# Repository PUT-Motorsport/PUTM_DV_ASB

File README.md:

# PUTM_DV_ASB_2023
Autonomus Brake System PCB and Software for PM07

Functionality:
Solenoid valves control,
Pressure sensors data acquisition,
Functional safety, and hard-wired logic implementation,
Autonomous System SDC driver,
RES communication bridge.

Important links:

FSG Rules:
fsg.one/rules

Previous board (unusable)

ASF Examples:
https://www.formulastudent.de/academy/hands-on/asf/

FSG Academy:
https://www.formulastudent.de/fileadmin/user_upload/all/2022/important_docs/FSG21_AS_Beginners_Guide_v1.0.pdf

Jakub's Mechanical construction:
https://files.podio.com/1561594165

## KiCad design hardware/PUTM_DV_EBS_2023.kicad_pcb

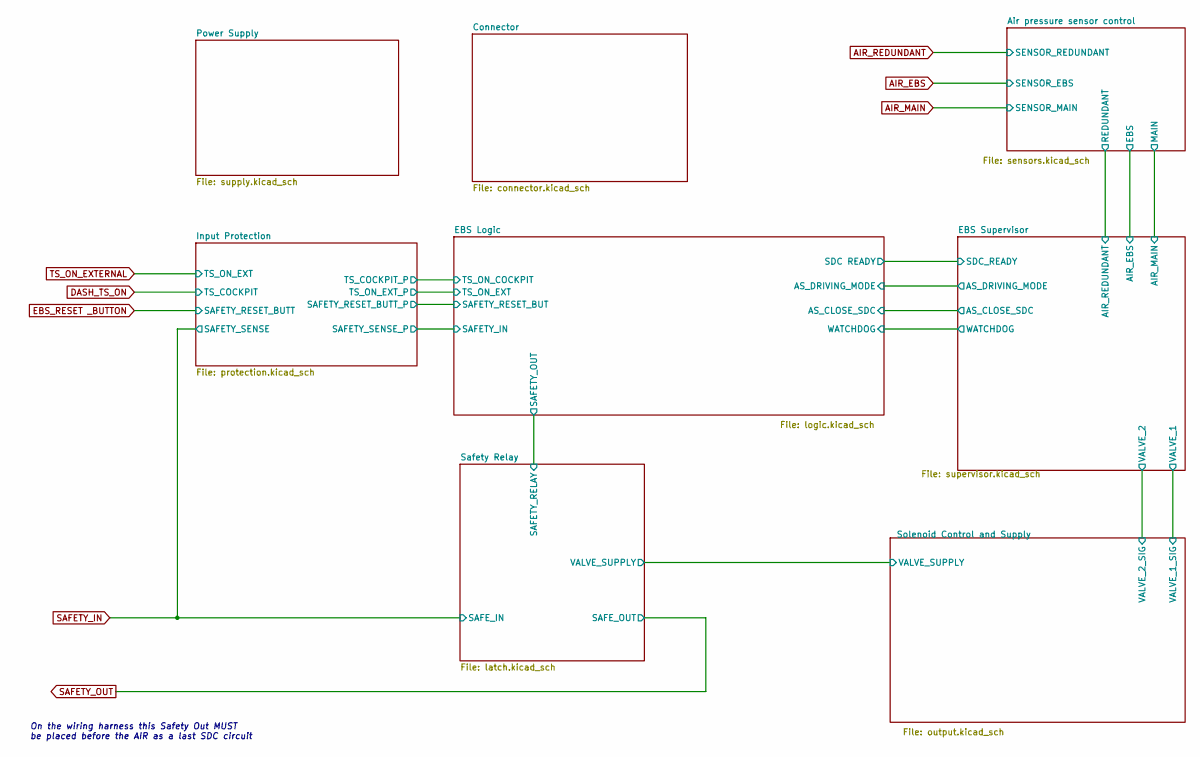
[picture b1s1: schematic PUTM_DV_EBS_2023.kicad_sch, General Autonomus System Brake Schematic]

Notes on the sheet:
On the wiring harness this Safety Out MUST be placed before the AIR as a last SDC circuit

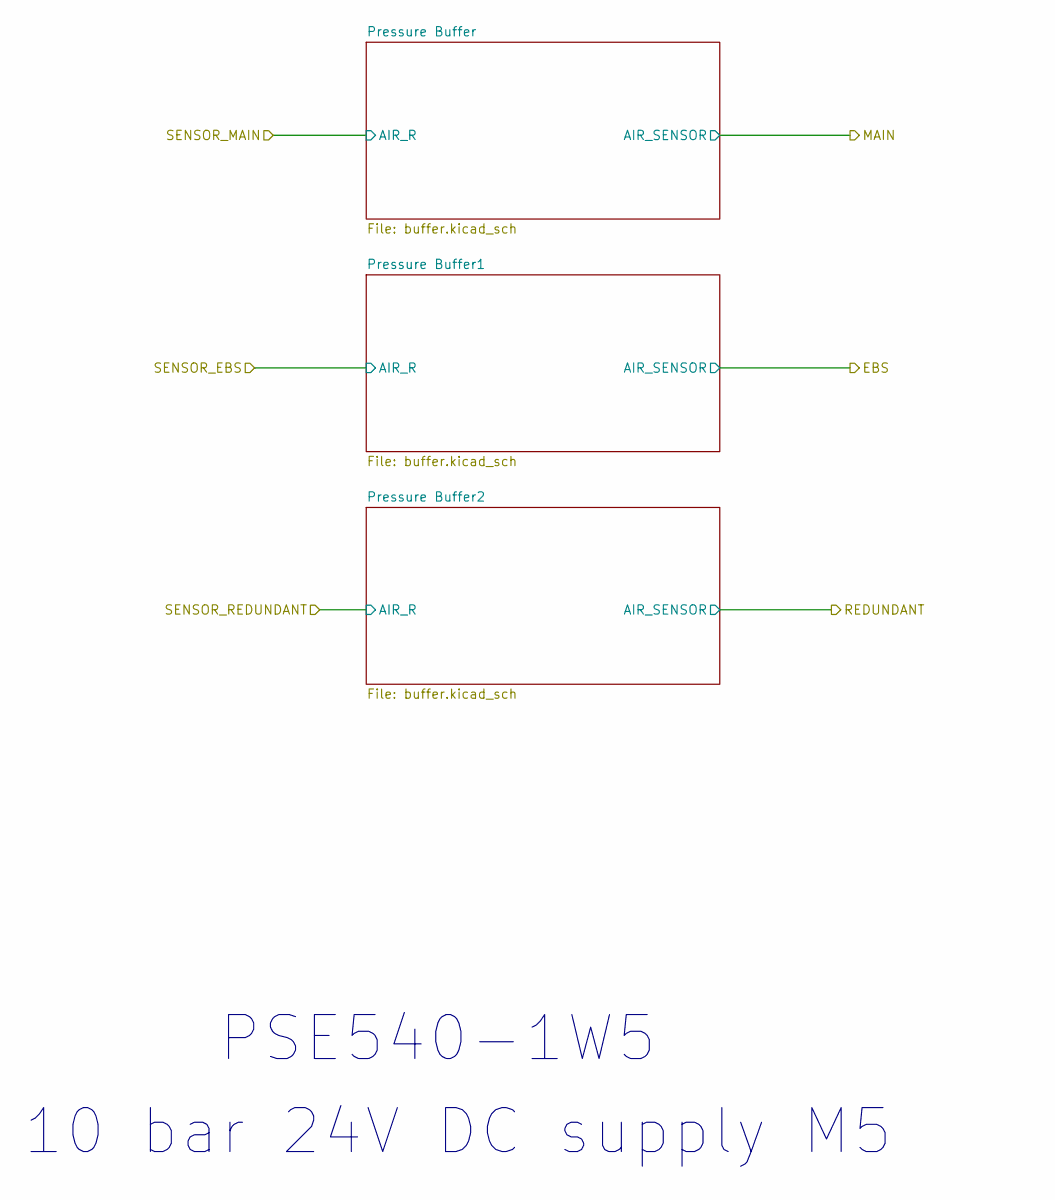
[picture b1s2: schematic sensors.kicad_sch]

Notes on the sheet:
10 bar 24V DC supply M5
PSE540-1W5

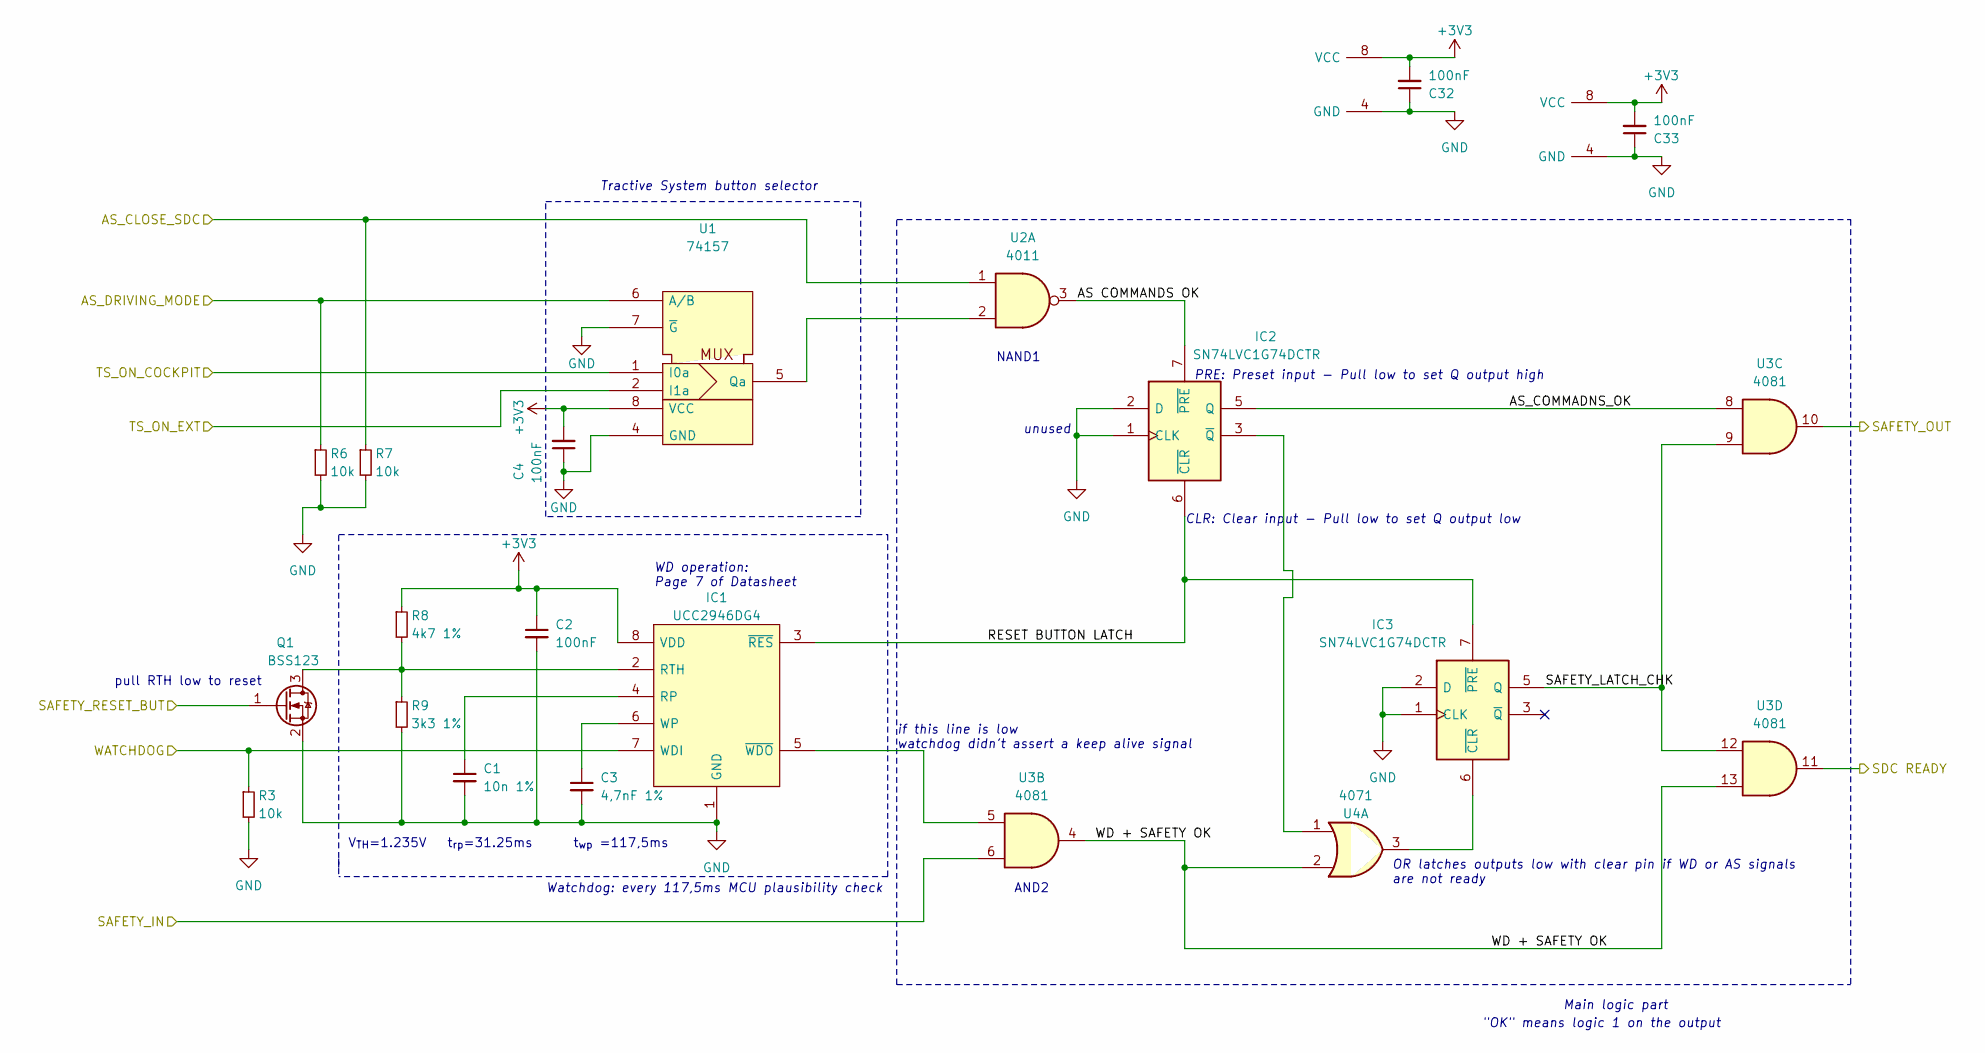
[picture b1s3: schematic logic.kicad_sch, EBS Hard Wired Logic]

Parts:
C1: 10n 1%; C_0603_1608Metric_Pad1.08x0.95mm_HandSolder
C2, C4, C32, C33: 100nF; C_0603_1608Metric_Pad1.08x0.95mm_HandSolder
C3: 4,7nF 1%; C_0603_1608Metric_Pad1.08x0.95mm_HandSolder
IC1: UCC2946DG4; SOIC127P600X175-8N; Mouser Part Number 595-UCC2946DG4
IC2, IC3: SN74LVC1G74DCTR; SOP65P400X130-8N; Mouser Part Number 595-SN74LVC1G74DCTR
Q1: BSS123; SOT-23
R3, R6, R7: 10k; R_0603_1608Metric_Pad0.98x0.95mm_HandSolder
R8: 4k7 1%; R_0603_1608Metric_Pad0.98x0.95mm_HandSolder
R9: 3k3 1%; R_0603_1608Metric_Pad0.98x0.95mm_HandSolder
U1: 74157; VSSOP-8_2.3x2mm_P0.5mm
U2: 4011; TSSOP-14_4.4x5mm_P0.65mm
U3: 4081; TSSOP-14_4.4x5mm_P0.65mm
U4: 4071; TSSOP-14_4.4x5mm_P0.65mm

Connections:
+3V3: C2.1, C4.2, C32.2, C33.2, IC1.8 (VDD), IC2.8 (VCC), IC3.8 (VCC), R8.1, U1.8 (VCC); also elsewhere on the board
/EBS Logic/AS COMMANDS OK: IC2.7 (~PRE), U2.3; also elsewhere on the board
/EBS Logic/AS_CLOSE_SDC: R7.1, U2.1; also elsewhere on the board
/EBS Logic/AS_COMMADNS_OK: IC2.5 (Q), U3.8
/EBS Logic/AS_DRIVING_MODE: R6.1, U1.6 (A/B); also elsewhere on the board
/EBS Logic/RESET BUTTON LATCH: IC1.3 (~RES), IC2.6 (~CLR), IC3.7 (~PRE); also elsewhere on the board
/EBS Logic/SAFETY_IN: U3.6; also elsewhere on the board
/EBS Logic/SAFETY_LATCH_CHK: IC3.5 (Q), U3.9, U3.12; also elsewhere on the board
/EBS Logic/SAFETY_OUT: U3.10; also elsewhere on the board
/EBS Logic/SAFETY_RESET_BUT: Q1.1 (G); also elsewhere on the board
/EBS Logic/SDC READY: U3.11; also elsewhere on the board
/EBS Logic/TS_ON_COCKPIT: U1.1 (I0a); also elsewhere on the board
/EBS Logic/TS_ON_EXT: U1.2 (I1a); also elsewhere on the board
/EBS Logic/WATCHDOG: IC1.7 (WDI), R3.1; also elsewhere on the board
/EBS Logic/WD + SAFETY OK: U3.4, U3.13, U4.2; also elsewhere on the board
GND: C1.2, C2.2, C3.2, C4.1, C32.1, C33.1, IC1.1 (GND), IC2.1 (CLK), IC2.2 (D), IC2.4 (GND), IC3.1 (CLK), IC3.2 (D), IC3.4 (GND), Q1.2 (S), R3.2, R6.2, R7.2, R9.2, U1.4 (GND), U1.7 (~G); also elsewhere on the board
unnamed: C1.1, IC1.4 (RP)
unnamed: C3.1, IC1.6 (WP)
unnamed 65: IC1.2 (RTH), Q1.3 (D), R8.2, R9.1; also elsewhere on the board
unnamed 66: IC1.5 (~WDO), U3.5; also elsewhere on the board
unnamed: IC2.3 (~Q), U4.1
unnamed: IC3.6 (~CLR), U4.3
unnamed: U1.5 (Qa), U2.2

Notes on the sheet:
OR latches outputs low with clear pin if WD or AS signals are not ready
unused
V_{TH}=1.235V
"OK" means logic 1 on the output
Watchdog: every 117,5ms MCU plausibility check
Tractive System button selector
pull RTH low to reset
PRE: Preset input − Pull low to set Q output high
Main logic part
CLR: Clear input − Pull low to set Q output low
AND2
NAND1
WD operation: Page 7 of Datasheet
if this line is low watchdog didn't assert a keep alive signal
t_{wp} =117,5ms
t_{rp}=31.25ms

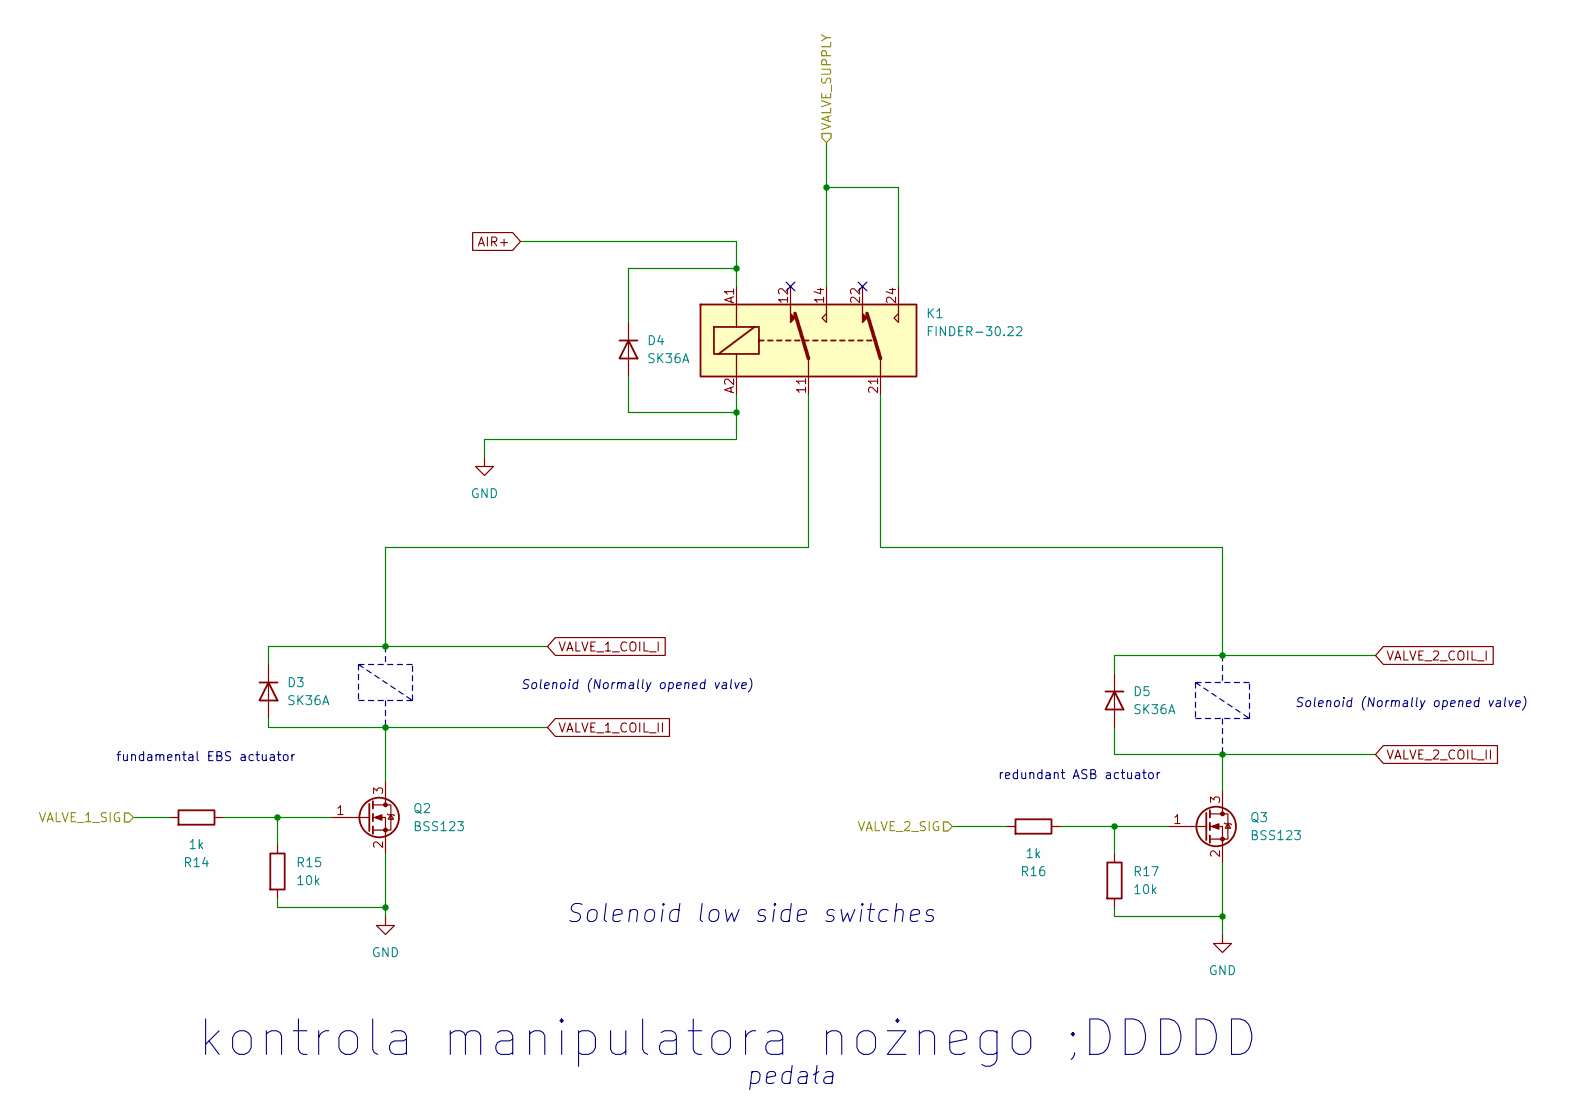
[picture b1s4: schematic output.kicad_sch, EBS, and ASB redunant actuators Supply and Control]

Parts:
D3, D4, D5: SK36A; D_SMA_Handsoldering
K1: FINDER-30.22; Relay_DPDT_Finder_30.22
Q2, Q3: BSS123; SOT-23
R14, R16: 1k; R_0603_1608Metric_Pad0.98x0.95mm_HandSolder
R15, R17: 10k; R_0603_1608Metric_Pad0.98x0.95mm_HandSolder

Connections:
/EBS Supervisor/VALVE_1: R14.2; also elsewhere on the board
/EBS Supervisor/VALVE_2: R16.2; also elsewhere on the board
/Safety Relay/VALVE_SUPPLY: K1.14, K1.24; also elsewhere on the board
AIR+: D4.1 (K), K1.A1; also elsewhere on the board
GND: D4.2 (A), K1.A2, Q2.2 (S), Q3.2 (S), R15.2, R17.2; also elsewhere on the board
unnamed: Q2.1 (G), R14.1, R15.1
unnamed: Q3.1 (G), R16.1, R17.1
VALVE_1_COIL_I: D3.1 (K), K1.11; also elsewhere on the board
VALVE_1_COIL_II: D3.2 (A), Q2.3 (D); also elsewhere on the board
VALVE_2_COIL_I: D5.1 (K), K1.21; also elsewhere on the board
VALVE_2_COIL_II: D5.2 (A), Q3.3 (D); also elsewhere on the board

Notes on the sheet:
Solenoid (Normally opened valve)
Solenoid low side switches
fundamental EBS actuator
pedała
redundant ASB actuator
kontrola manipulatora nożnego ;DDDDD

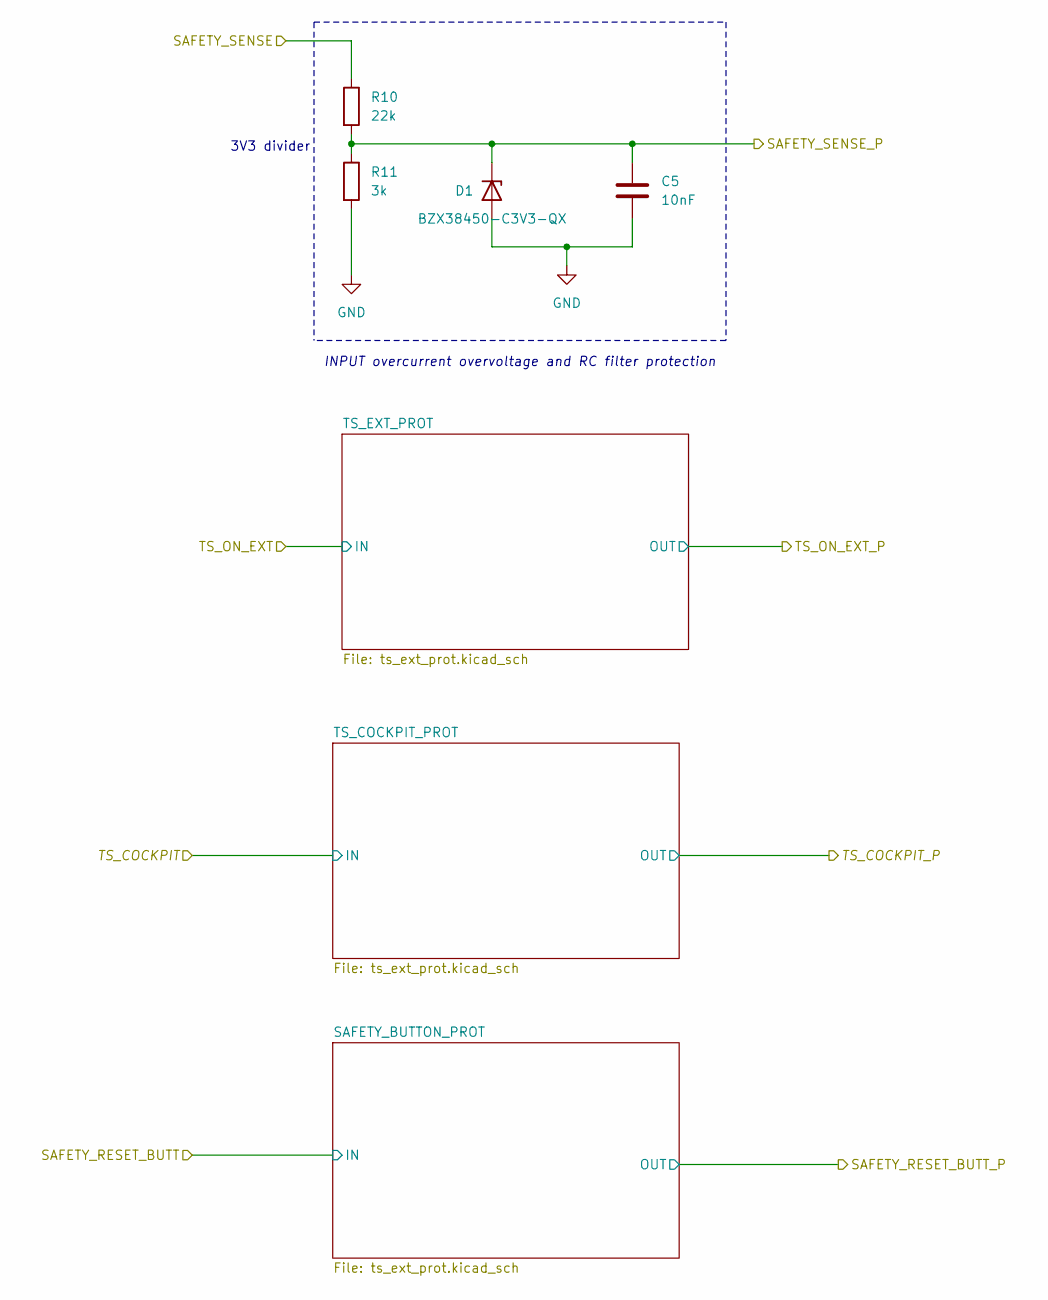
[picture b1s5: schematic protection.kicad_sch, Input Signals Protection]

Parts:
C5: 10nF; C_0603_1608Metric_Pad1.08x0.95mm_HandSolder
D1: BZX38450-C3V3-QX; D_SOD-323_HandSoldering
R10: 22k; R_0603_1608Metric_Pad0.98x0.95mm_HandSolder
R11: 3k; R_0603_1608Metric_Pad0.98x0.95mm_HandSolder

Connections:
/EBS Logic/SAFETY_IN: C5.1, D1.1 (K), R10.2, R11.1; also elsewhere on the board
GND: C5.2, D1.2 (A), R11.2; also elsewhere on the board
SAFETY_IN: R10.1; also elsewhere on the board

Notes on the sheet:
3V3 divider
INPUT overcurrent overvoltage and RC filter protection

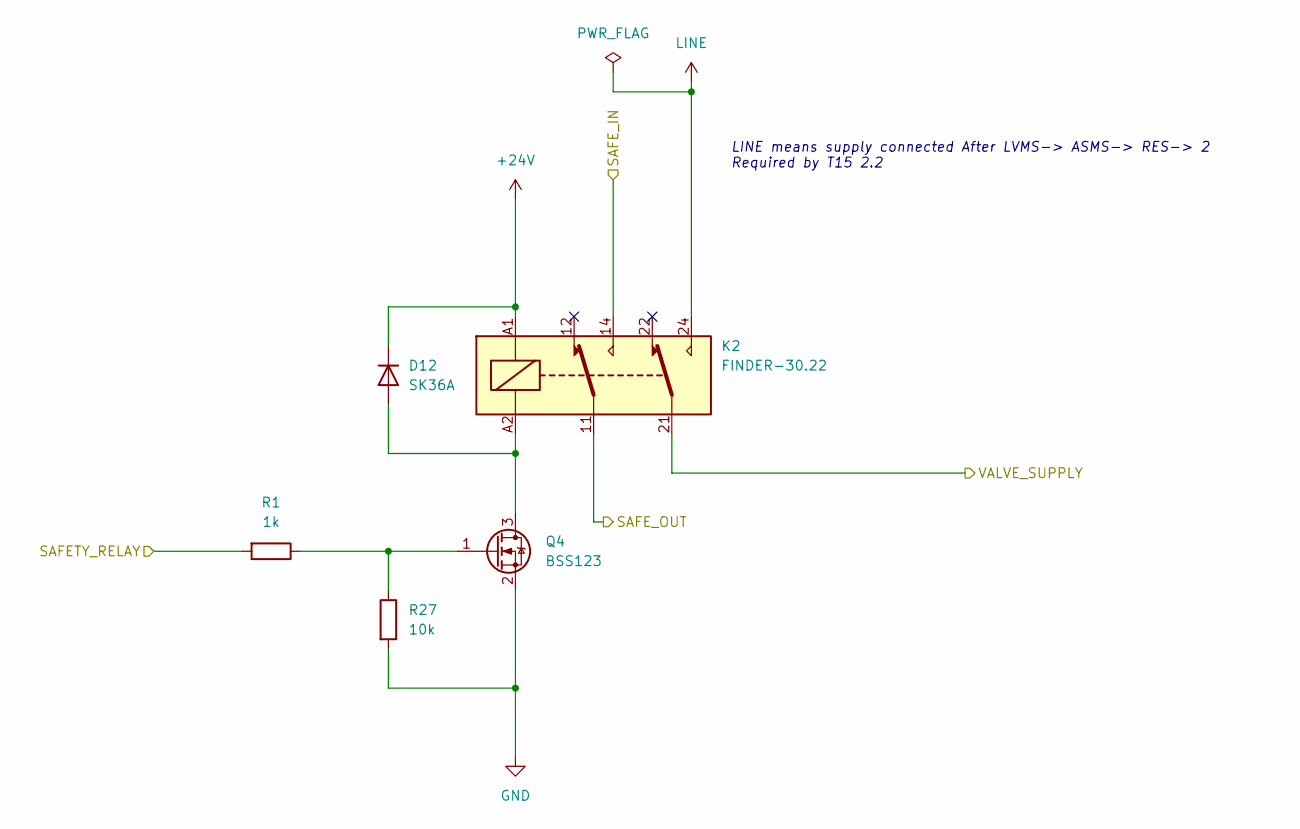
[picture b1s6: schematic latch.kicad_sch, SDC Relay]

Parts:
D12: SK36A; D_SMA_Handsoldering
K2: FINDER-30.22; Relay_DPDT_Finder_30.22
Q4: BSS123; SOT-23
R1: 1k; R_0603_1608Metric_Pad0.98x0.95mm_HandSolder
R27: 10k; R_0603_1608Metric_Pad0.98x0.95mm_HandSolder

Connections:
+24V: D12.1 (K), K2.A1; also elsewhere on the board
/EBS Logic/SAFETY_OUT: R1.2; also elsewhere on the board
/Safety Relay/VALVE_SUPPLY: K2.21; also elsewhere on the board
GND: Q4.2 (S), R27.2; also elsewhere on the board
LINE: K2.24; also elsewhere on the board
unnamed: D12.2 (A), K2.A2, Q4.3 (D)
unnamed: Q4.1 (G), R1.1, R27.1
SAFETY_IN: K2.14; also elsewhere on the board
SAFETY_OUT: K2.11; also elsewhere on the board

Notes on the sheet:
LINE means supply connected After LVMS-> ASMS-> RES-> 2 Required by T15 2.2

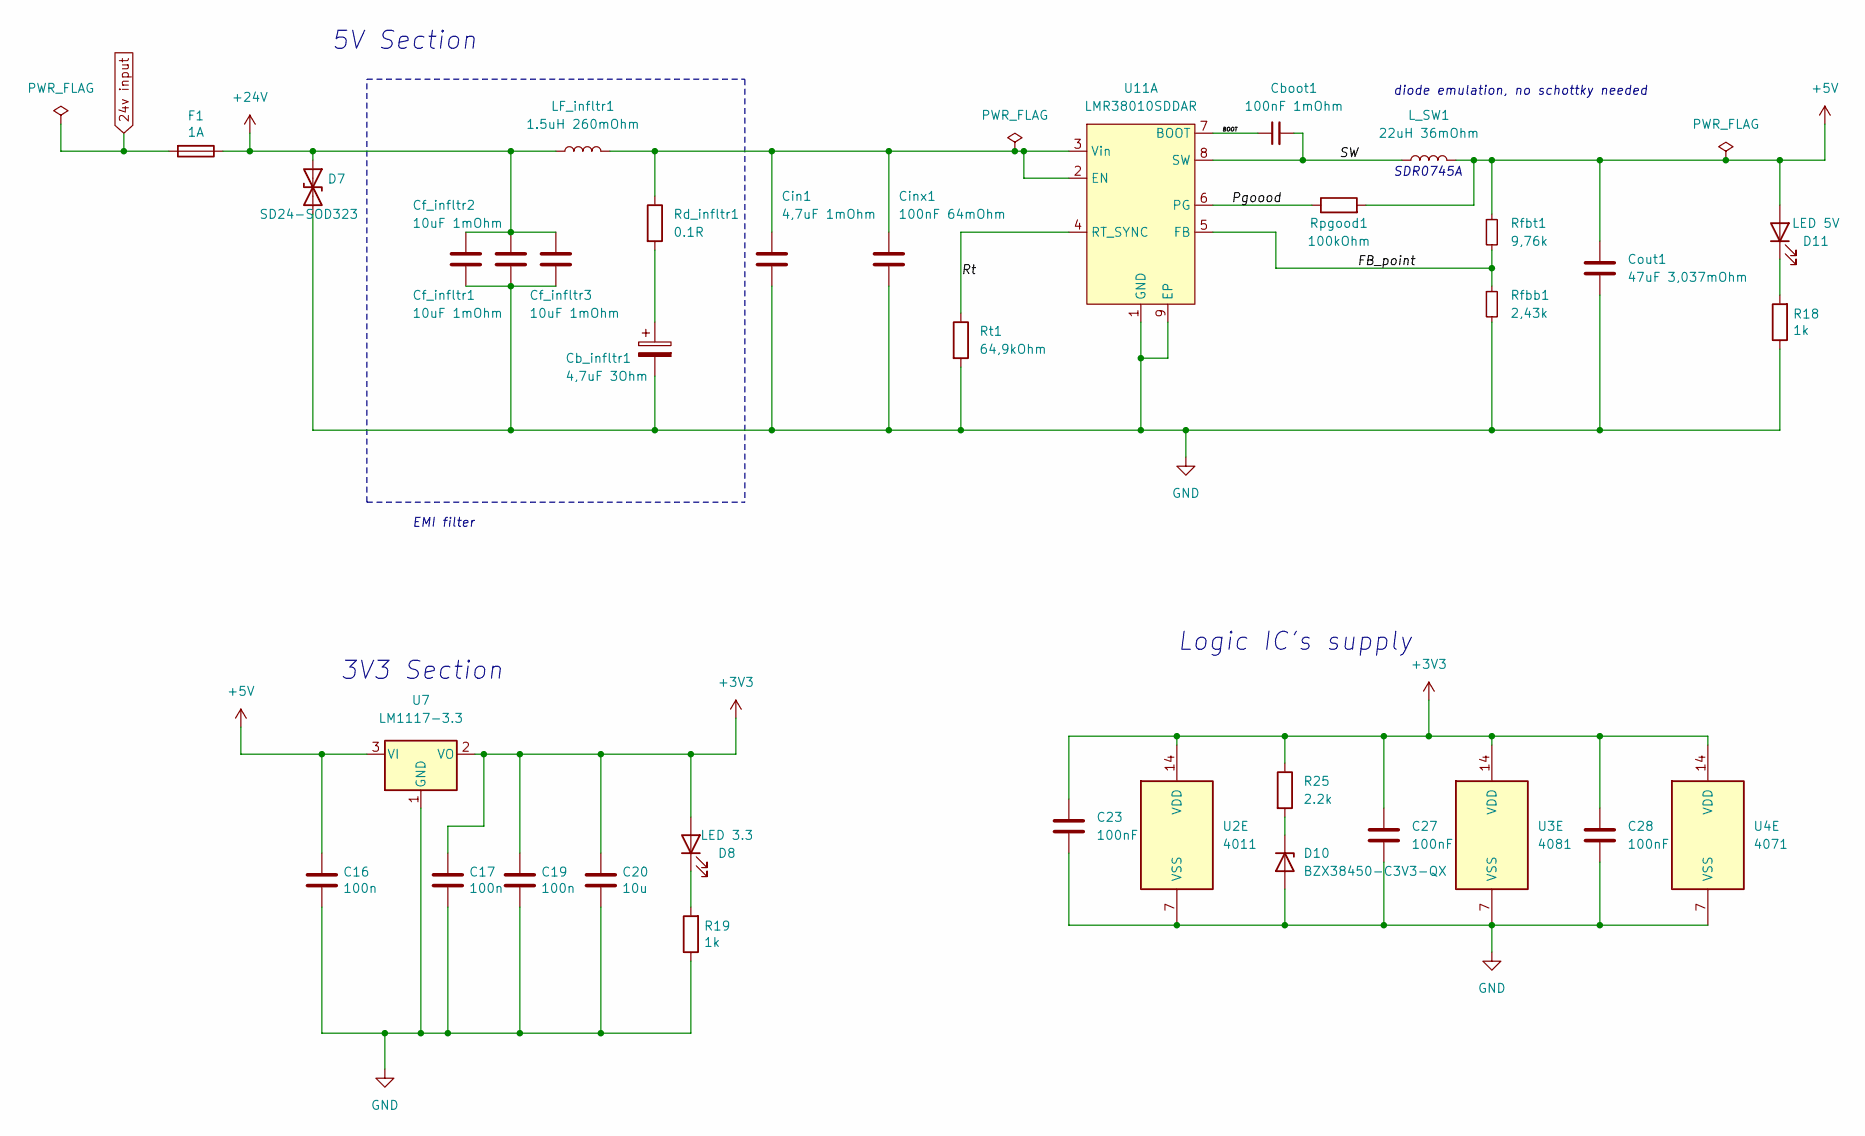
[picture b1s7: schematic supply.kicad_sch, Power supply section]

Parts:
C16, C17, C19: 100n; C_0603_1608Metric_Pad1.08x0.95mm_HandSolder
C20: 10u; C_0603_1608Metric_Pad1.08x0.95mm_HandSolder
C23: 100nF; C_0201_0603Metric_Pad0.64x0.40mm_HandSolder
C27, C28: 100nF; C_0603_1608Metric_Pad1.08x0.95mm_HandSolder
Cb_infltr1: 4,7uF 3Ohm; CP_Elec_4x5.4
Cboot1: 100nF 1mOhm; C_0402_1005Metric_Pad0.74x0.62mm_HandSolder
Cf_infltr1, Cf_infltr2, Cf_infltr3: 10uF 1mOhm; C_1210_3225Metric_Pad1.33x2.70mm_HandSolder
Cin1: 4,7uF 1mOhm; C_0805_2012Metric_Pad1.18x1.45mm_HandSolder
Cinx1: 100nF 64mOhm; C_0805_2012Metric_Pad1.18x1.45mm_HandSolder
Cout1: 47uF 3,037mOhm; C_1206_3216Metric_Pad1.33x1.80mm_HandSolder
D7: SD24-SOD323; D_SMB
D8: LED 3.3; LED_0603_1608Metric_Pad1.05x0.95mm_HandSolder
D10: BZX38450-C3V3-QX; D_SOD-323_HandSoldering
D11: LED 5V; LED_0603_1608Metric_Pad1.05x0.95mm_HandSolder
F1: 1A; Fuse_1206_3216Metric
LF_infltr1: 1.5uH 260mOhm; L_0805_2012Metric_Pad1.05x1.20mm_HandSolder
L_SW1: 22uH 36mOhm; L_Bourns_EBS
R18, R19: 1k; R_0603_1608Metric_Pad0.98x0.95mm_HandSolder
R25: 2.2k; R_0603_1608Metric_Pad0.98x0.95mm_HandSolder
Rd_infltr1: 0.1R; R_0603_1608Metric_Pad0.98x0.95mm_HandSolder
Rfbb1: 2,43k; R_0402_1005Metric_Pad0.72x0.64mm_HandSolder
Rfbt1: 9,76k; R_0402_1005Metric_Pad0.72x0.64mm_HandSolder
Rpgood1: 100kOhm; R_0603_1608Metric_Pad0.98x0.95mm_HandSolder
Rt1: 64,9kOhm; R_0603_1608Metric_Pad0.98x0.95mm_HandSolder
U2: 4011; TSSOP-14_4.4x5mm_P0.65mm
U3: 4081; TSSOP-14_4.4x5mm_P0.65mm
U4: 4071; TSSOP-14_4.4x5mm_P0.65mm
U7: LM1117-3.3; TO-252-3_TabPin2
U11: LMR38010SDDAR; TI_SO-PowerPAD-8_ThermalVias

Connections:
24v input: F1.2; also elsewhere on the board
+3V3: C17.1, C19.1, C20.1, C23.1, C27.1, C28.1, D8.2 (A), R25.1, U2.14 (VDD), U3.14 (VDD), U4.14 (VDD), U7.2 (VO); also elsewhere on the board
+5V: C16.1, Cout1.1, D11.2 (A), L_SW1.2, Rfbt1.1, Rpgood1.2, U7.3 (VI); also elsewhere on the board
+24V: Cf_infltr1.1, Cf_infltr2.1, Cf_infltr3.1, D7.1 (A1), F1.1, LF_infltr1.1; also elsewhere on the board
/Power Supply/BOOT: Cboot1.1, U11.7 (BOOT)
/Power Supply/FB_point: Rfbb1.1, Rfbt1.2, U11.5 (FB)
/Power Supply/Pgoood: Rpgood1.1, U11.6 (PG)
/Power Supply/Rt: Rt1.1, U11.4 (RT_SYNC)
/Power Supply/SW: Cboot1.2, L_SW1.1, U11.8 (SW)
GND: C16.2, C17.2, C19.2, C20.2, C23.2, C27.2, C28.2, Cb_infltr1.2, Cf_infltr1.2, Cf_infltr2.2, Cf_infltr3.2, Cin1.2, Cinx1.2, Cout1.2, D7.2 (A2), D10.2 (A), R18.1, R19.1, Rfbb1.2, Rt1.2, U2.7 (VSS), U3.7 (VSS), U4.7 (VSS), U7.1 (GND), U11.1 (GND), U11.9 (EP); also elsewhere on the board
unnamed: Cb_infltr1.1, Rd_infltr1.2
unnamed: Cin1.1, Cinx1.1, LF_infltr1.2, Rd_infltr1.1, U11.2 (EN), U11.3 (Vin)
unnamed: D8.1 (K), R19.2
unnamed: D10.1 (K), R25.2
unnamed: D11.1 (K), R18.2

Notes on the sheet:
diode emulation, no schottky needed
3V3 Section
EMI filter
Logic IC's supply
5V Section
SDR0745A

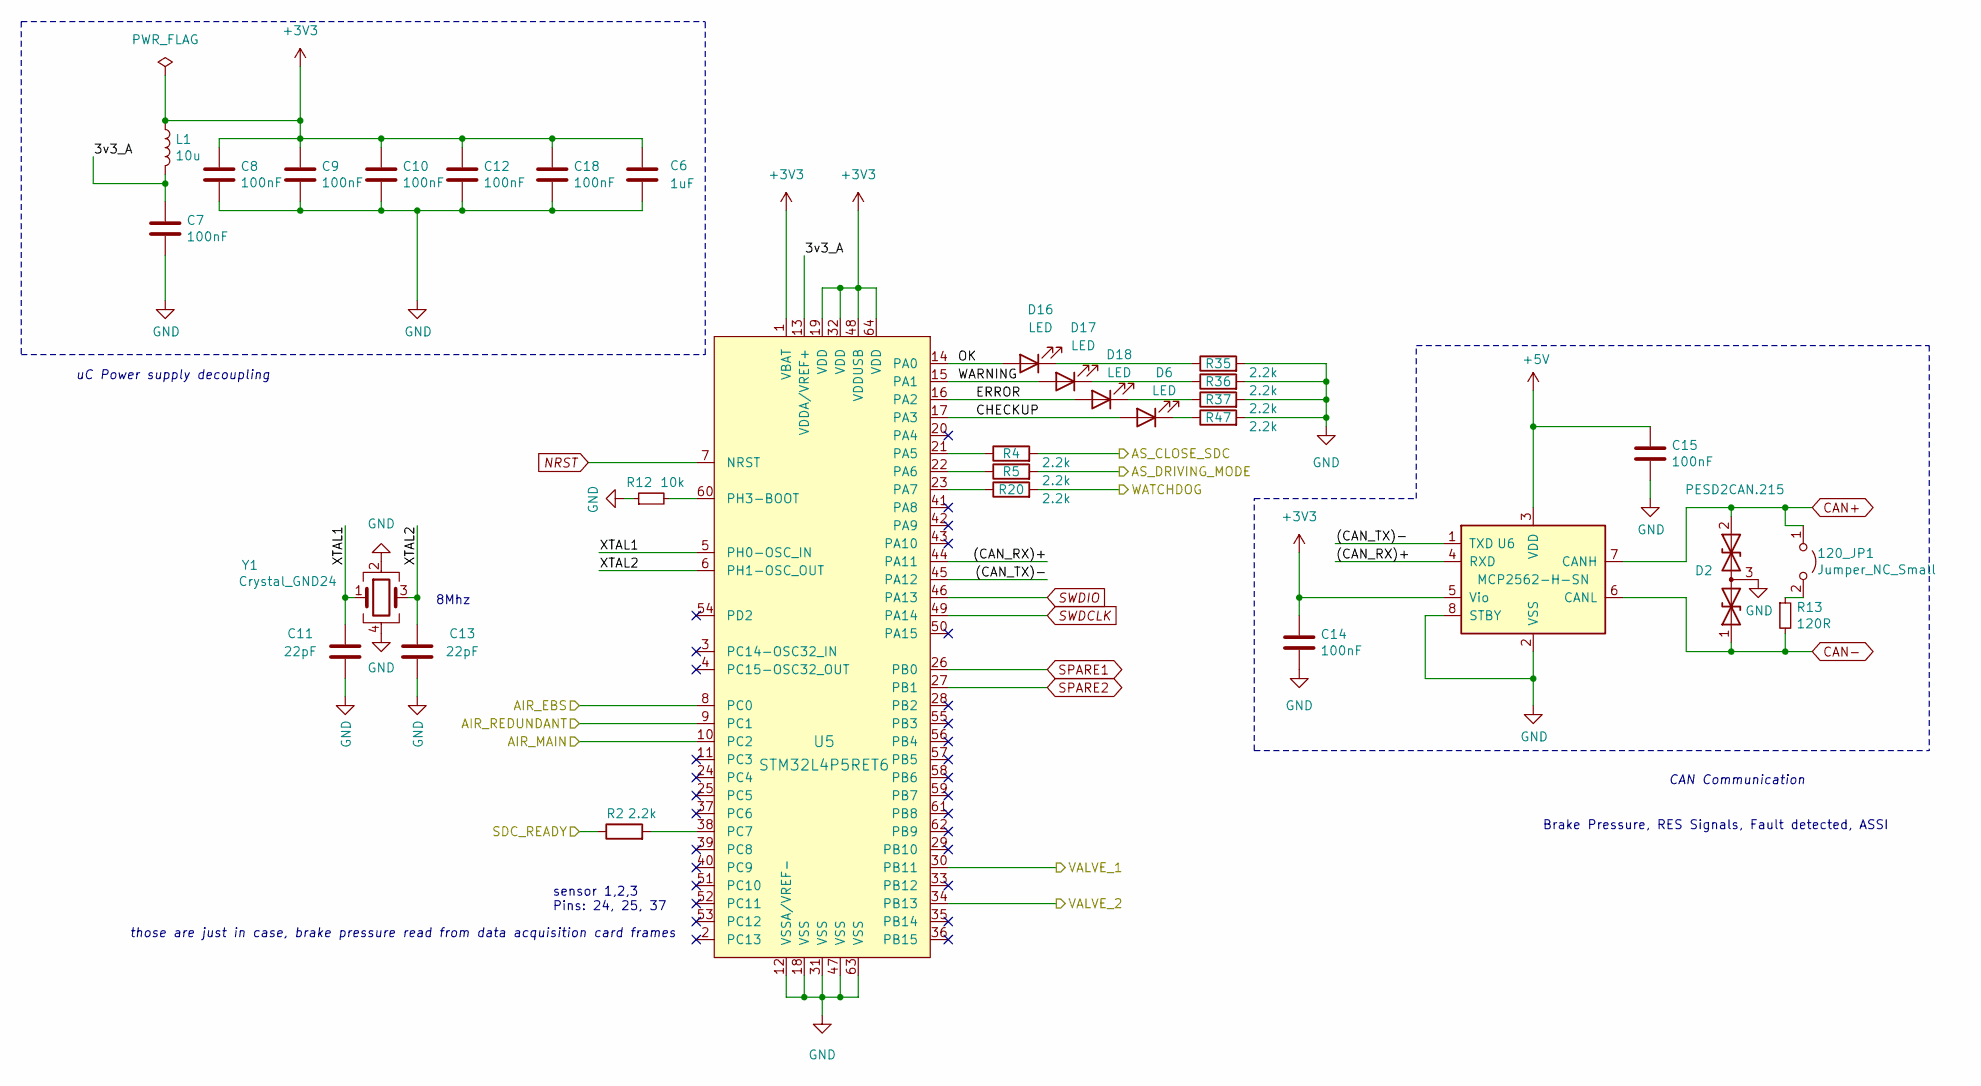
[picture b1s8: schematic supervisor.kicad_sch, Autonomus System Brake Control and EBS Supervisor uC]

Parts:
120_JP1: Jumper_NC_Small; PinHeader_1x02_P2.54mm_Vertical
C6: 1uF; C_0603_1608Metric_Pad1.08x0.95mm_HandSolder
C7, C8, C9, C10, C12, C14, C18: 100nF; C_0603_1608Metric_Pad1.08x0.95mm_HandSolder
C11, C13: 22pF; C_0603_1608Metric_Pad1.08x0.95mm_HandSolder
C15: 100nF; C_0805_2012Metric_Pad1.18x1.45mm_HandSolder
D2: PESD2CAN.215; SOT-23
D6, D16, D17, D18: LED; LED_0603_1608Metric_Pad1.05x0.95mm_HandSolder
L1: 10u; L_0805_2012Metric
R2, R4, R5, R20, R35, R36, R37, R47: 2.2k; R_0603_1608Metric_Pad0.98x0.95mm_HandSolder
R12: 10k; R_0603_1608Metric_Pad0.98x0.95mm_HandSolder
R13: 120R; R_0603_1608Metric_Pad0.98x0.95mm_HandSolder
U5: STM32L4P5RET6; LQFP-64_10x10mm_P0.5mm
U6: MCP2562-H-SN; SOIC-8_3.9x4.9mm_P1.27mm
Y1: Crystal_GND24; Crystal_SMD_3225-4Pin_3.2x2.5mm

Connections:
+3V3: C6.1, C8.1, C9.1, C10.1, C12.1, C14.1, C18.1, L1.1, U5.1 (VBAT), U5.19 (VDD), U5.32 (VDD), U5.48 (VDDUSB), U5.64 (VDD), U6.5 (Vio); also elsewhere on the board
+5V: C15.1, U6.3 (VDD); also elsewhere on the board
/Air pressure sensor control/EBS: U5.8 (PC0); also elsewhere on the board
/Air pressure sensor control/MAIN: U5.10 (PC2); also elsewhere on the board
/Air pressure sensor control/REDUNDANT: U5.9 (PC1); also elsewhere on the board
/EBS Logic/AS_CLOSE_SDC: R4.2; also elsewhere on the board
/EBS Logic/AS_DRIVING_MODE: R5.2; also elsewhere on the board
/EBS Logic/SDC READY: R2.1; also elsewhere on the board
/EBS Logic/WATCHDOG: R20.2; also elsewhere on the board
/EBS Supervisor/3v3_A: C7.1, L1.2, U5.13 (VDDA/VREF+)
/EBS Supervisor/(CAN_RX)+: U5.44 (PA11), U6.4 (RXD)
/EBS Supervisor/(CAN_TX)-: U5.45 (PA12), U6.1 (TXD)
/EBS Supervisor/CHECKUP: D6.2 (A), U5.17 (PA3)
/EBS Supervisor/ERROR: D18.2 (A), U5.16 (PA2)
/EBS Supervisor/OK: D16.2 (A), U5.14 (PA0)
/EBS Supervisor/VALVE_1: U5.30 (PB11); also elsewhere on the board
/EBS Supervisor/VALVE_2: U5.34 (PB13); also elsewhere on the board
/EBS Supervisor/WARNING: D17.2 (A), U5.15 (PA1)
/EBS Supervisor/XTAL1: C11.1, U5.5 (PH0-OSC_IN), Y1.1
/EBS Supervisor/XTAL2: C13.1, U5.6 (PH1-OSC_OUT), Y1.3
CAN+: 120_JP1.1 (A), D2.2 (A2), U6.7 (CANH); also elsewhere on the board
CAN-: D2.1 (A1), R13.2, U6.6 (CANL); also elsewhere on the board
GND: C6.2, C7.2, C8.2, C9.2, C10.2, C11.2, C12.2, C13.2, C14.2, C15.2, C18.2, D2.3 (common), R12.1, R35.2, R36.2, R37.2, R47.2, U5.12 (VSSA/VREF-), U5.18 (VSS), U5.31 (VSS), U5.47 (VSS), U5.63 (VSS), U6.2 (VSS), U6.8 (STBY), Y1.2, Y1.4; also elsewhere on the board
NRST: U5.7 (NRST); also elsewhere on the board
unnamed: 120_JP1.2 (B), R13.1
unnamed: D6.1 (K), R47.1
unnamed: D16.1 (K), R35.1
unnamed: D17.1 (K), R36.1
unnamed: D18.1 (K), R37.1
unnamed: R2.2, U5.38 (PC7)
unnamed: R4.1, U5.21 (PA5)
unnamed: R5.1, U5.22 (PA6)
unnamed: R12.2, U5.60 (PH3-BOOT)
unnamed: R20.1, U5.23 (PA7)
SWDCLK: U5.49 (PA14); also elsewhere on the board
SWDIO: U5.46 (PA13); also elsewhere on the board

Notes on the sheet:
CAN Communication
those are just in case, brake pressure read from data acquisition card frames
sensor 1,2,3 Pins: 24, 25, 37
8Mhz
uC Power supply decoupling
Brake Pressure, RES Signals, Fault detected, ASSI

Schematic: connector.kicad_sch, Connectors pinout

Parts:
J1: SAFETY_SUPPLY; M80-5L104YYMC
J2: SWDIO_CONN; PinHeader_1x05_P2.54mm_Vertical
J3: SENSORS; M80-5L104YYMC
J4: VALVES; M80-5L104YYMC
J5: MAIN; M80-5L112YYMC

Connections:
24v input: J5.5; also elsewhere on the board
+3V3: J2.1; also elsewhere on the board
AIR+: J5.12; also elsewhere on the board
AIR_EBS: J3.3; also elsewhere on the board
AIR_MAIN: J3.2; also elsewhere on the board
AIR_REDUNDANT: J3.1; also elsewhere on the board
CAN+: J5.7; also elsewhere on the board
CAN-: J5.1; also elsewhere on the board
DASH_TS_ON: J5.2; also elsewhere on the board
EBS_RESET _BUTTON: J5.3; also elsewhere on the board
GND: J2.3, J5.6; also elsewhere on the board
LINE: J1.3; also elsewhere on the board
NRST: J2.5; also elsewhere on the board
SAFETY_IN: J1.2; also elsewhere on the board
SAFETY_OUT: J1.4; also elsewhere on the board
SWDCLK: J2.2; also elsewhere on the board
SWDIO: J2.4; also elsewhere on the board
TS_ON_EXTERNAL: J5.8; also elsewhere on the board
VALVE_1_COIL_I: J4.1; also elsewhere on the board
VALVE_1_COIL_II: J4.3; also elsewhere on the board
VALVE_2_COIL_I: J4.2; also elsewhere on the board
VALVE_2_COIL_II: J4.4; also elsewhere on the board

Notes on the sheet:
10pin version not in stock ;/
HARWIN J-TEK
Connectors are divided intentionaly- Clue is to speed up inspection process where scrutineer will be unplugging different things and checking functional safety of the system
M80-5L11242MC
(AFTER RES 2)
M80-5L10442MC
so they are divided to sections to speed it up

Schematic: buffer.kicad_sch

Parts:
C34: 5.6n; C_0603_1608Metric_Pad1.08x0.95mm_HandSolder
C37: 100nF; C_0603_1608Metric
R38: 3.3k 1%; R_0603_1608Metric_Pad0.98x0.95mm_HandSolder
R39: 6.8k 1%; R_0603_1608Metric_Pad0.98x0.95mm_HandSolder
R40: 1k; R_0603_1608Metric_Pad0.98x0.95mm_HandSolder
U8: type="X" model="TSX7191" lib=""; SOT-23-5_HandSoldering

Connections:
+5V: C37.1, U8.4 (V+); also elsewhere on the board
/Air pressure sensor control/MAIN: R40.2; also elsewhere on the board
AIR_MAIN: R38.1; also elsewhere on the board
GND: C34.2, C37.2, R39.2, U8.5 (V-); also elsewhere on the board
unnamed: C34.1, R38.2, R39.1, U8.1 (+)
unnamed: R40.1, U8.2 (-), U8.3

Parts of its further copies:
C35, C36: 5.6n; C_0603_1608Metric_Pad1.08x0.95mm_HandSolder
C38, C39: 100nF; C_0603_1608Metric
R41, R44: 3.3k 1%; R_0603_1608Metric_Pad0.98x0.95mm_HandSolder
R42, R45: 6.8k 1%; R_0603_1608Metric_Pad0.98x0.95mm_HandSolder
R43, R46: 1k; R_0603_1608Metric_Pad0.98x0.95mm_HandSolder

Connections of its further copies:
+5V: C38.1, C39.1; also elsewhere on the board
/Air pressure sensor control/EBS: R43.2; also elsewhere on the board
/Air pressure sensor control/REDUNDANT: R46.2; also elsewhere on the board
AIR_EBS: R41.1; also elsewhere on the board
AIR_REDUNDANT: R44.1; also elsewhere on the board
GND: C35.2, C36.2, C38.2, C39.2, R42.2, R45.2; also elsewhere on the board
unnamed 53: C35.1, R41.2, R42.1; also elsewhere on the board
unnamed 54: C36.1, R44.2, R45.1; also elsewhere on the board
unnamed 78: R43.1; also elsewhere on the board
unnamed 79: R46.1; also elsewhere on the board

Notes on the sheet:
1k(sens out z)
PSE output impedance= 1kOhm

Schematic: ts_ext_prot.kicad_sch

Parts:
C29: 10nF; C_0603_1608Metric_Pad1.08x0.95mm_HandSolder
D13: BZX38450-C3V3-QX; D_SOD-323_HandSoldering
R28: 22k; R_0603_1608Metric_Pad0.98x0.95mm_HandSolder
R29: 3k; R_0603_1608Metric_Pad0.98x0.95mm_HandSolder

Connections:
/EBS Logic/TS_ON_EXT: C29.1, D13.1 (K), R28.2, R29.1; also elsewhere on the board
GND: C29.2, D13.2 (A), R29.2; also elsewhere on the board
TS_ON_EXTERNAL: R28.1; also elsewhere on the board

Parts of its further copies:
C30, C31: 10nF; C_0603_1608Metric_Pad1.08x0.95mm_HandSolder
D14, D15: BZX38450-C3V3-QX; D_SOD-323_HandSoldering
R30, R32: 22k; R_0603_1608Metric_Pad0.98x0.95mm_HandSolder
R31, R33: 3k; R_0603_1608Metric_Pad0.98x0.95mm_HandSolder

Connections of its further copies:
/EBS Logic/SAFETY_RESET_BUT: C31.1, D15.1 (K), R32.2, R33.1; also elsewhere on the board
/EBS Logic/TS_ON_COCKPIT: C30.1, D14.1 (K), R30.2, R31.1; also elsewhere on the board
DASH_TS_ON: R30.1; also elsewhere on the board
EBS_RESET _BUTTON: R32.1; also elsewhere on the board
GND: C30.2, C31.2, D14.2 (A), D15.2 (A), R31.2, R33.2; also elsewhere on the board

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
